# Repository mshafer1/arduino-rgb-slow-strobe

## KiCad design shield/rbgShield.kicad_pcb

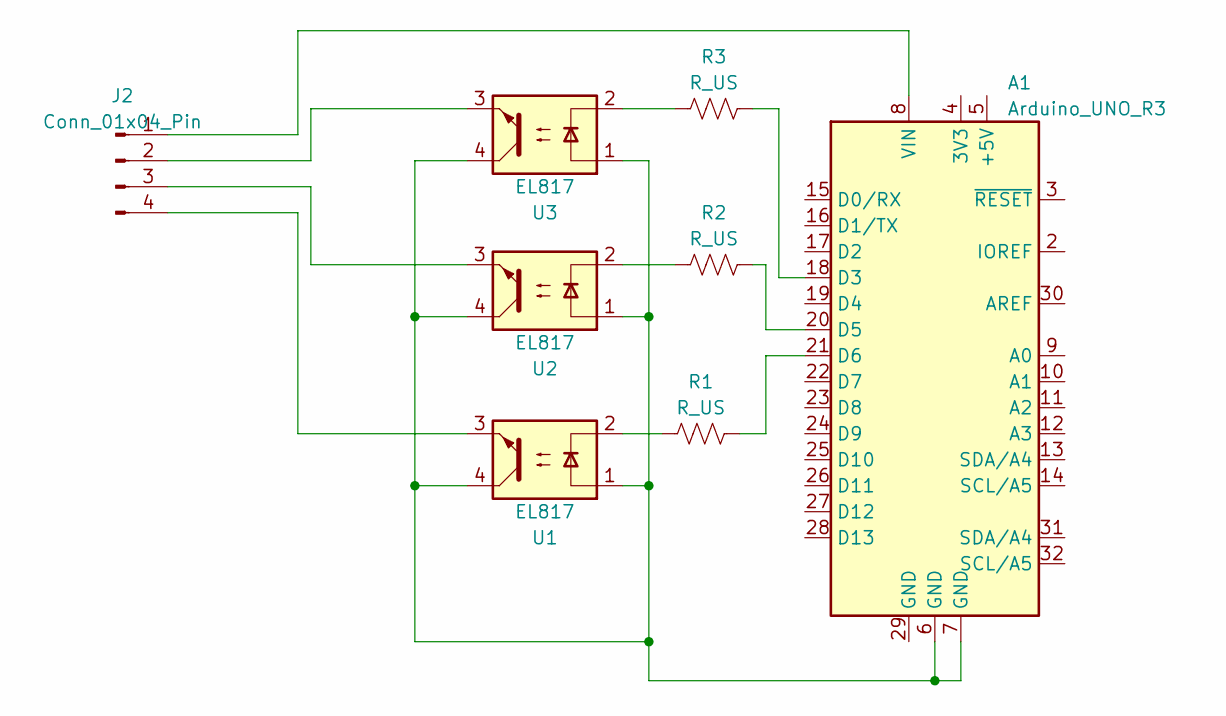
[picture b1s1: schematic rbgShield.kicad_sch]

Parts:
A1: Arduino_UNO_R3
J2: Conn_01x04_Pin; FanPinHeader_1x04_P2.54mm_Vertical
R1, R2, R3: R_US; R_Axial_DIN0204_L3.6mm_D1.6mm_P7.62mm_Horizontal
U1, U2, U3: EL817; DIP-4_W7.62mm

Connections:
unnamed: A1.18 (D3), R3.2
unnamed: A1.20 (D5), R2.2
unnamed: A1.21 (D6), R1.2
unnamed: A1.6 (GND), A1.7 (GND), U1.1, U1.4, U2.1, U2.4, U3.1, U3.4
unnamed: A1.8 (VIN), J2.1
unnamed: J2.2, U3.3
unnamed: J2.3, U2.3
unnamed: J2.4, U1.3
unnamed: R1.1, U1.2
unnamed: R2.1, U2.2
unnamed: R3.1, U3.2

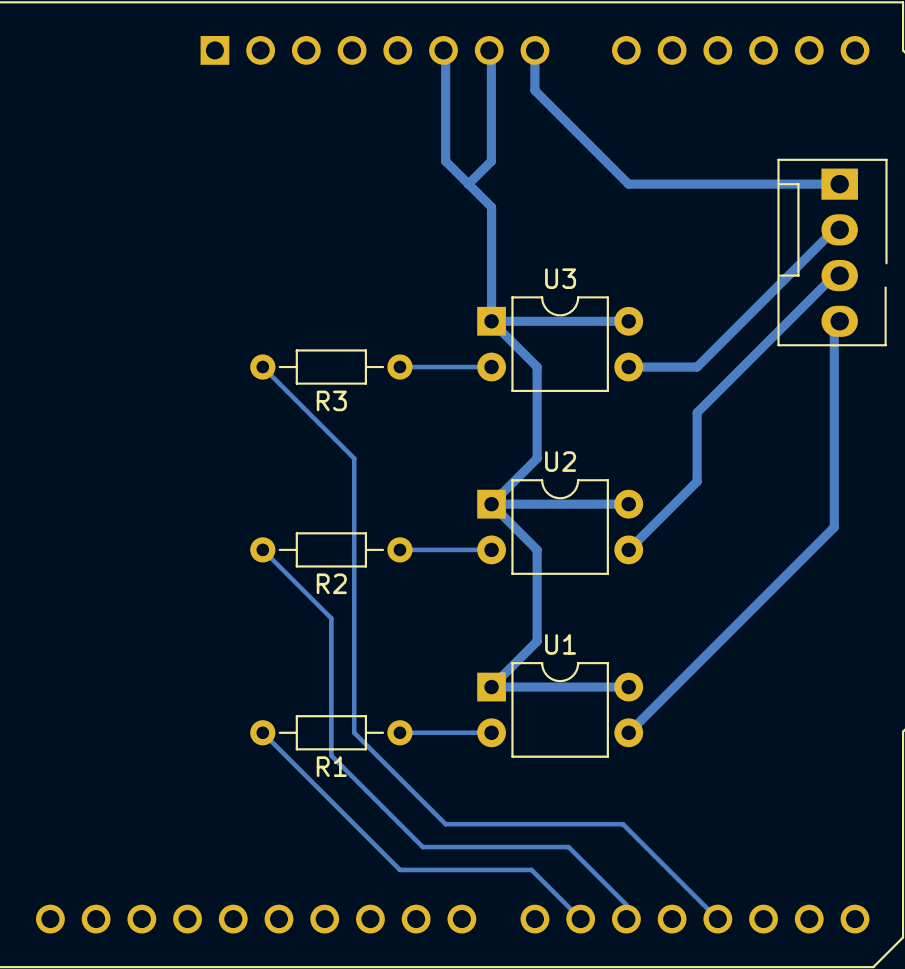
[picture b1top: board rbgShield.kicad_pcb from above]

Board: 2 copper layers, 8 parts (0 on the bottom side), 11 nets.

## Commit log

2023-05-28 init
2023-12-17 add kicad shield
2023-12-17 update code for shield
2023-12-17 Swap the pin order
    The pins swap order as they go through the opto-couplers, so wiring the strip "RGB"-Ground results in incorrect colors. This is an unfortunate example of changing software to fix a hardware bug.
